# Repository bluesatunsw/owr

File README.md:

# owr
This repo includes all software necessary to operate the Test Rover Platform
that is being designed and developed in the OWR project.
=======

## System Setup
A guide is available on the
[owr-docs](https://github.com/bluesatunsw/owr-docs/tree/main/src/guides/container_setup.md)
repository.

## Useful Command index
| Command                                                               | Effect                                                                                          |
| -------------------------------                                       | --------------------------------                                                                |
| `podman compose -f "$PWD/.devcontainer/docker-compose.yml" up -d`     | Run in the git root to build/restart/start the Docker container.                                |
| `podman compose -f "$PWD/.devcontainer/docker-compose-obc.yml" up -d` | Run in the git root to build/restart/start the Docker container **with obc specific settings!** |
| `podman exec -it --latest /bin/bash`                                  | Enter the docker container after launching it with the devcontainer.                            |
| `./utils/init.bash`                                                   | Run after `cd`'ing into `/workspaces/owr` in the container to source the ROS env and tools      |
| `colcon build --symlink-install`                                      | Runs the `colcon` meta build system, builds ALL rover packages!                                 |
| `ros2 launch rover rover.launch.py`                                   | Launch the robot state publisher. Just leave this running.                                      |
| `rqt`                                                                 | The flexible ROS2 viewer, useful for debugging topic flows and looking at raw topics.           |
| `rviz2`                                                               | Useful for visualizing TF2 / LiDAR / etc... data to see if it looks okay.                       |
| `podman rm --force --latest -t 0`                                     | Kill the podman container with the latest creation date (quickly)                               |

NOTE: `podman compose` will take a VERY long time! on uni Wi-Fi \~5min due to
the amount of packages it installs (\~5GB). There is also [a podman
bug](github.com/containers/podman/issues/16541) that invokes a postprocessing
step on the overlay filesystem, this will take **upwards of 10 minutes!** 

NOTE: `./utils/init.bash` will source the appropriate files as well as put you
in a 10-deep nested shell - running an invalid command will kill 1 level!

### Less Common Commands

| Command                                                               | Effect                                                                                    |
| -------------------------------                                       | --------------------------------                                                          |
| `ros2 launch rover rsp.launch.py`                                     | Robot State Publisher, publishes the URDF+JSP, to make it viewable in Lichtblick / Rviz2. |
| `xacro ./src/rover/description/robot.urdf.xacro > ./build/rover.urdf` | Compiles the xacro into a singular urdf file                                              |
| `ros2 run key_teleop key_teleop --ros-args -p twist_stamped_enabled:=True -r /key_vel:=/diff_drive_base_controller/cmd_vel` | Record keyboard imputs and publish them as Twist2d values, which ROS2Control is listening for!

### Useful Podman Commands
| Command                                                               | Effect                                                                                    |
| -------------------------------                                       | ---------------------------------                                                         |
| `podman images`                                                       | Lists current podman images                                                               |
| `podman rmi {ID} --force`                                             | Remove relevant image. Replace the ID with output from the above command                  |

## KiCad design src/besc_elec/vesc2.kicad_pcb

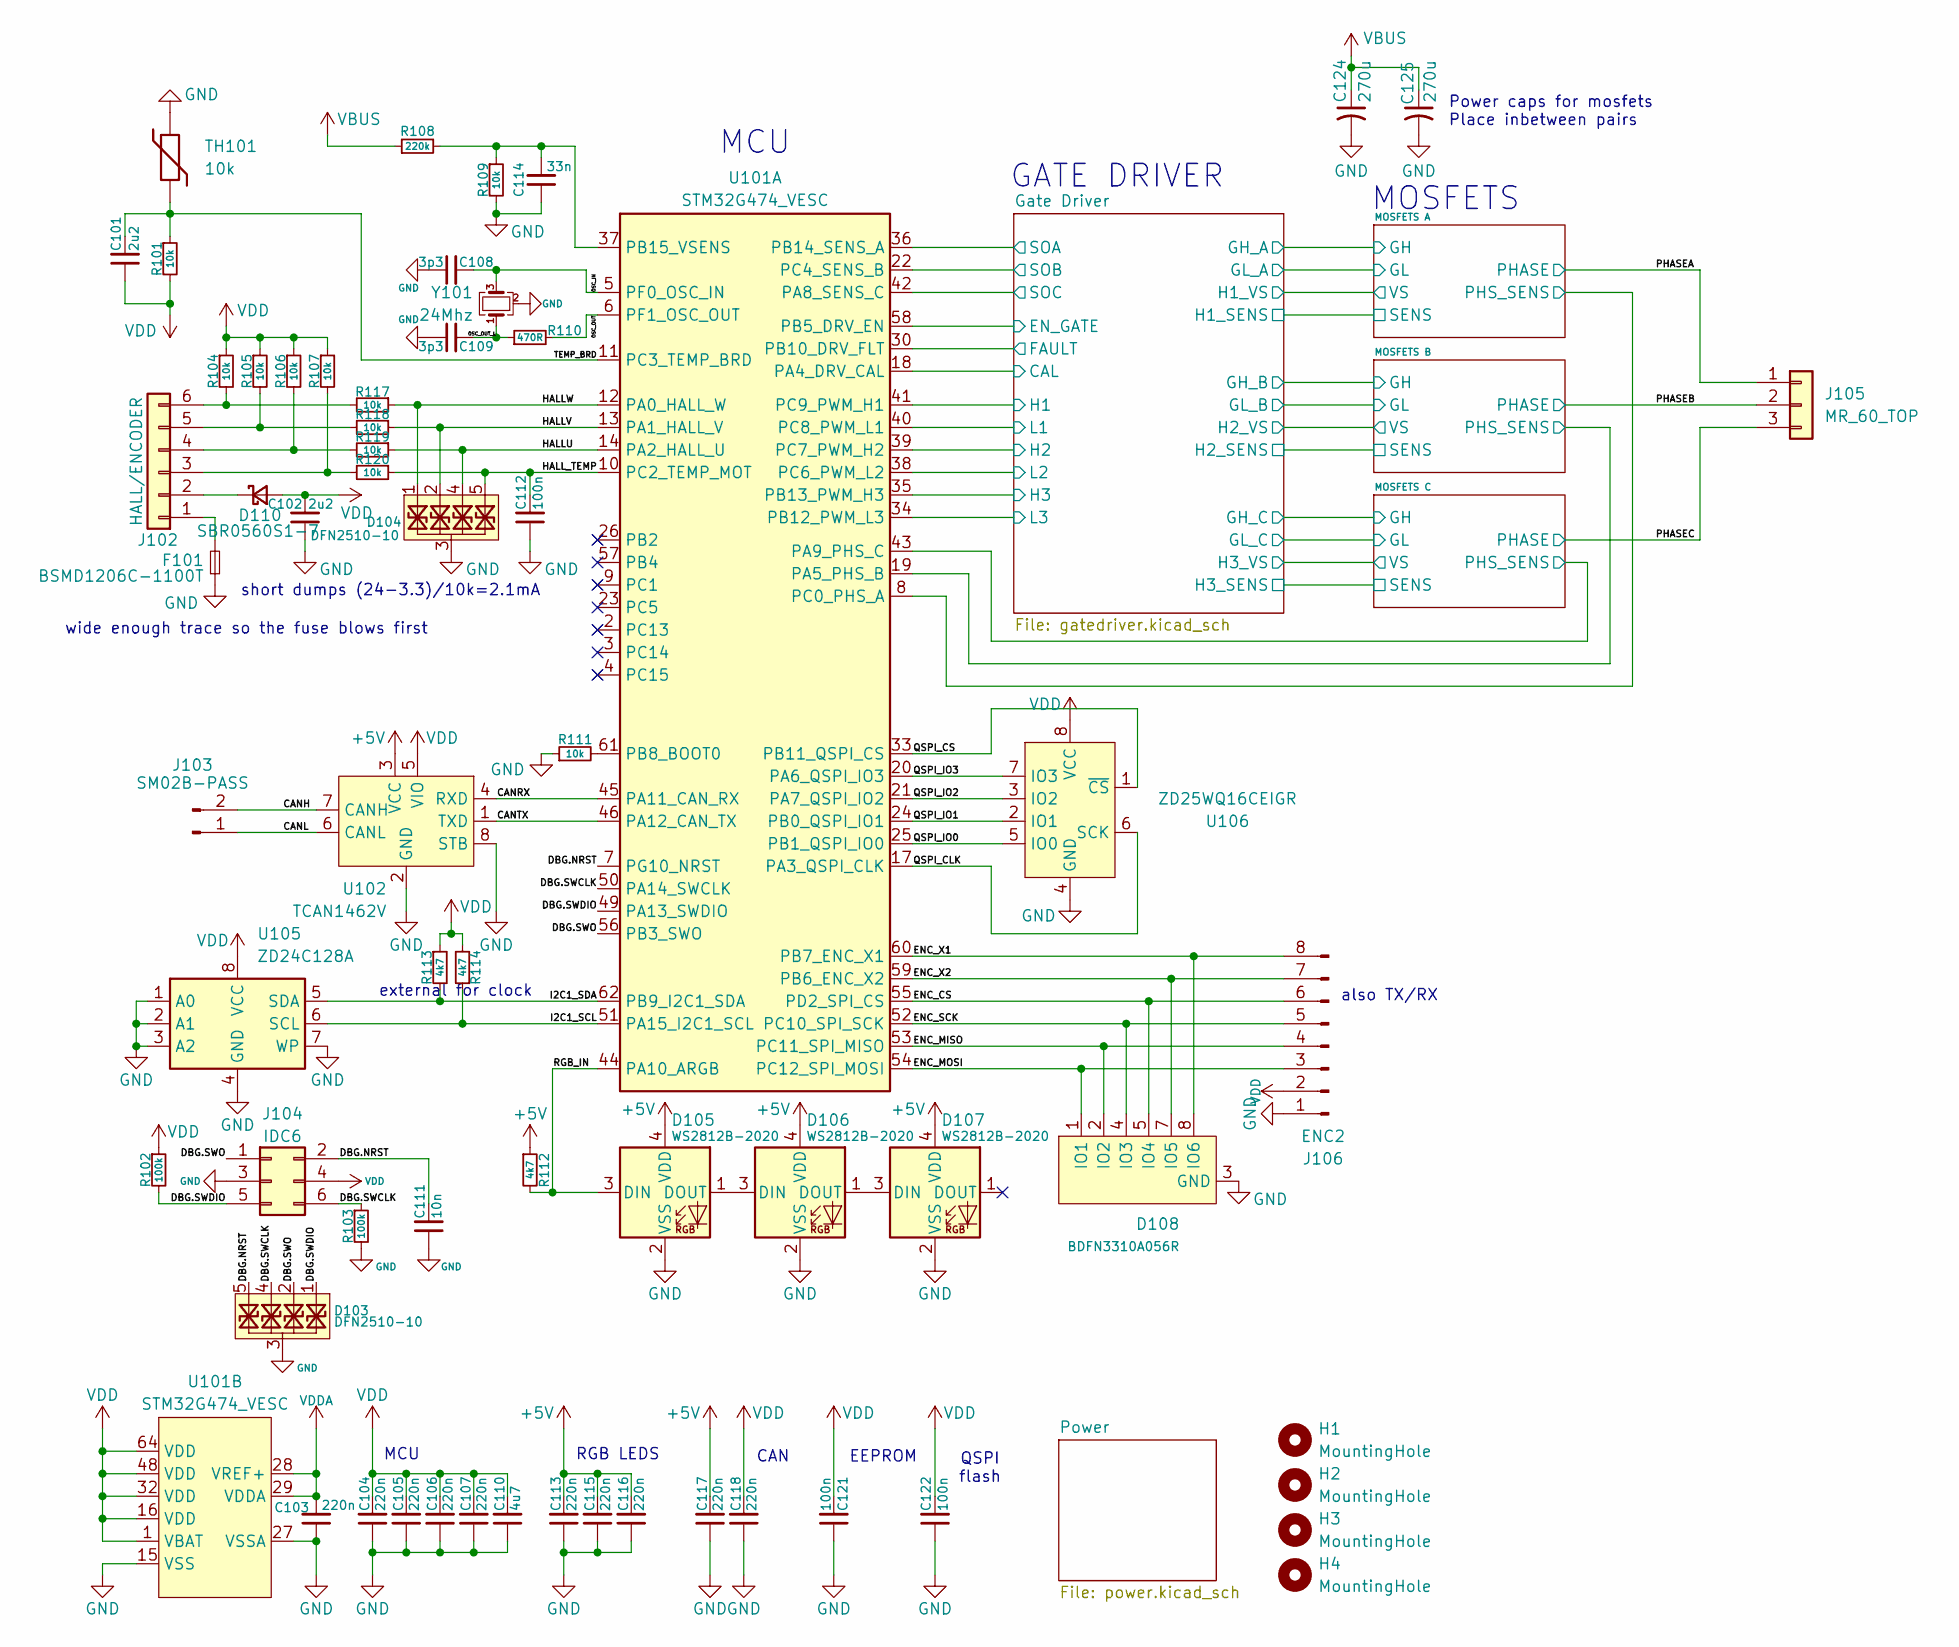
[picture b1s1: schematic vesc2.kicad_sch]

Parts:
C101, C102: 2u2; C_0603_1608Metric
C103, C104, C105, C106, C107, C113, C115, C116, C117, C118: 220n; C_0402_1005Metric
C108, C109: 3p3; C_0402_1005Metric
C110: 4u7; C_0805_2012Metric
C111: 10n; C_0402_1005Metric
C112, C121, C122: 100n; C_0402_1005Metric
C114: 33n; C_0402_1005Metric
C124, C125: 270u; CP_Elec_10x10
D103, D104: DFN2510-10; Diodes_UDFN-10_1x2.5mm_P0.5mm
D105, D106, D107: WS2812B-2020; LED_WS2812B-2020_PLCC4_2.0x2.0mm
D108: BDFN3310A056R; UDFN8_3P3X1_517CB_ONS
D110: SBR0560S1-7; D_SOD-123
F101: BSMD1206C-1100T; Fuse_1206_3216Metric
H1, H2, H3, H4: MountingHole; bluesatM2.5
J102: HALL/ENCODER; BM06B-PASS
J103: SM02B-PASS; BM02B-PASS
J104: IDC6
J105: MR_60_TOP; MR60-F-TopMount
J106: ENC2; JST_PH_B8B-PH-SM4-TB_1x08-1MP_P2.00mm_Vertical
R101, R104, R105, R106, R107, R109, R111, R117, R118, R119, R120: 10k; R_0402_1005Metric
R102, R103: 100k; R_0402_1005Metric
R108: 220k; R_0402_1005Metric
R110: 470R; R_0402_1005Metric
R112, R113, R114: 4k7; R_0402_1005Metric
TH101: 10k; R_0402_1005Metric
U101: STM32G474_VESC; LQFP-64-0.5
U102: TCAN1462V; SOIC-8_3.9x4.9mm_P1.27mm
U105: ZD24C128A; TSSOP-8_4.4x3.0-0.65
U106: ZD25WQ16CEIGR; Winbond_USON-8-1EP_3x2mm_P0.5mm_EP0.2x1.6mm
Y101: 24Mhz; Crystal_SMD_2016-4Pin_2.0x1.6mm

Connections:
+5V: C113.2, C115.2, C116.2, C117.2, D105.4 (VDD), D106.4 (VDD), D107.4 (VDD), R112.1, U102.3 (VCC); also elsewhere on the board
/CANH: J103.2, U102.7 (CANH)
/CANL: J103.1, U102.6 (CANL)
/CANRX: U101.45 (PA11_CAN_RX), U102.4 (RXD)
/CANTX: U101.46 (PA12_CAN_TX), U102.1 (TXD)
/DBG.NRST: C111.2, D103.5, D103.6, J104.2, U101.7 (PG10_NRST)
/DBG.SWCLK: D103.4, D103.7, J104.6, R103.1, U101.50 (PA14_SWCLK)
/DBG.SWDIO: D103.1, D103.10, J104.5, R102.2, U101.49 (PA13_SWDIO)
/DBG.SWO: D103.2, D103.9, J104.1, U101.56 (PB3_SWO)
/ENC_CS: D108.5 (IO4), J106.6, U101.55 (PD2_SPI_CS)
/ENC_MISO: D108.2 (IO2), J106.4, U101.53 (PC11_SPI_MISO)
/ENC_MOSI: D108.1 (IO1), J106.3, U101.54 (PC12_SPI_MOSI)
/ENC_SCK: D108.4 (IO3), J106.5, U101.52 (PC10_SPI_SCK)
/ENC_X1: D108.8 (IO6), J106.8, U101.60 (PB7_ENC_X1)
/ENC_X2: D108.7 (IO5), J106.7, U101.59 (PB6_ENC_X2)
/Gate Driver/CAL: U101.18 (PA4_DRV_CAL); also elsewhere on the board
/Gate Driver/EN_GATE: U101.58 (PB5_DRV_EN); also elsewhere on the board
/Gate Driver/FAULT: U101.30 (PB10_DRV_FLT); also elsewhere on the board
/Gate Driver/H1: U101.41 (PC9_PWM_H1); also elsewhere on the board
/Gate Driver/H2: U101.39 (PC7_PWM_H2); also elsewhere on the board
/Gate Driver/H3: U101.35 (PB13_PWM_H3); also elsewhere on the board
/Gate Driver/L1: U101.40 (PC8_PWM_L1); also elsewhere on the board
/Gate Driver/L2: U101.38 (PC6_PWM_L2); also elsewhere on the board
/Gate Driver/L3: U101.34 (PB12_PWM_L3); also elsewhere on the board
/Gate Driver/SOA: U101.36 (PB14_SENS_A); also elsewhere on the board
/Gate Driver/SOB: U101.22 (PC4_SENS_B); also elsewhere on the board
/Gate Driver/SOC: U101.42 (PA8_SENS_C); also elsewhere on the board
/HALLU: D104.4, D104.7, R119.1, U101.14 (PA2_HALL_U)
/HALLV: D104.2, D104.9, R118.1, U101.13 (PA1_HALL_V)
/HALLW: D104.1, D104.10, R117.1, U101.12 (PA0_HALL_W)
/HALL_TEMP: C112.2, D104.5, D104.6, R120.1, U101.10 (PC2_TEMP_MOT)
/I2C1_SCL: R114.1, U101.51 (PA15_I2C1_SCL), U105.6 (SCL)
/I2C1_SDA: R113.2, U101.62 (PB9_I2C1_SDA), U105.5 (SDA)
/MOSFETS A/PHS_SENS: U101.8 (PC0_PHS_A); also elsewhere on the board
/MOSFETS B/PHS_SENS: U101.19 (PA5_PHS_B); also elsewhere on the board
/MOSFETS C/PHS_SENS: U101.43 (PA9_PHS_C); also elsewhere on the board
/OSC_IN: C108.2, U101.5 (PF0_OSC_IN), Y101.3
/OSC_OUT: R110.2, U101.6 (PF1_OSC_OUT)
/OSC_OUT_L: C109.2, R110.1, Y101.1
/PHASEA: J105.1; also elsewhere on the board
/PHASEB: J105.2; also elsewhere on the board
/PHASEC: J105.3; also elsewhere on the board
/QSPI_CLK: U101.17 (PA3_QSPI_CLK), U106.6 (SCK)
/QSPI_CS: U101.33 (PB11_QSPI_CS), U106.1 (~CS)
/QSPI_IO0: U101.25 (PB1_QSPI_IO0), U106.5 (IO0)
/QSPI_IO1: U101.24 (PB0_QSPI_IO1), U106.2 (IO1)
/QSPI_IO2: U101.21 (PA7_QSPI_IO2), U106.3 (IO2)
/QSPI_IO3: U101.20 (PA6_QSPI_IO3), U106.7 (IO3)
/RGB_IN: D105.3 (DIN), R112.2, U101.44 (PA10_ARGB)
/TEMP_BRD: C101.2, R101.1, TH101.2, U101.11 (PC3_TEMP_BRD)
GND: C102.1, C103.1, C104.1, C105.1, C106.1, C107.1, C108.1, C109.1, C110.1, C111.1, C112.1, C113.1, C114.1, C115.1, C116.1, C117.1, C118.1, C121.1, C122.1, C124.2, C125.2, D103.3, D103.8, D104.3, D104.8, D105.2 (VSS), D106.2 (VSS), D107.2 (VSS), D108.3 (GND), D108.6 (GND), D108.9 (GND), D108.10 (GND), F101.1, J104.3, J106.1, J106.MP (EP), R103.2, R109.2, R111.1, TH101.1, U101.15 (VSS), U101.27 (VSSA), U101.31 (VSS), U101.47 (VSS), U101.63 (VSS), U102.2 (GND), U102.8 (STB), U102.9 (EP), U105.1 (A0), U105.2 (A1), U105.3 (A2), U105.4 (GND), U105.7 (WP), U106.4 (GND), U106.9 (EP), Y101.2 (G), Y101.4 (G); also elsewhere on the board
unnamed: D105.1 (DOUT), D106.3 (DIN)
unnamed: D106.1 (DOUT), D107.3 (DIN)
unnamed: D110.1 (K), J102.2
unnamed: F101.2, J102.1
unnamed: J102.3, R107.2, R120.2
unnamed: J102.4, R106.2, R119.2
unnamed: J102.5, R105.2, R118.2
unnamed: J102.6, R104.2, R117.2
unnamed: R111.2, U101.61 (PB8_BOOT0)
unnamed: C114.2, R108.2, R109.1, U101.37 (PB15_VSENS)
VBUS: C124.1, C125.1, R108.1; also elsewhere on the board
VDD: C101.1, C102.2, C104.2, C105.2, C106.2, C107.2, C110.2, C118.2, C121.2, C122.2, D110.2 (A), J104.4, J106.2, R101.2, R102.1, R104.1, R105.1, R106.1, R107.1, R113.1, R114.2, U101.1 (VBAT), U101.16 (VDD), U101.32 (VDD), U101.48 (VDD), U101.64 (VDD), U102.5 (VIO), U105.8 (VCC), U106.8 (VCC); also elsewhere on the board
VDDA: C103.2, U101.28 (VREF+), U101.29 (VDDA); also elsewhere on the board

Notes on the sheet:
EEPROM
RGB LEDS
Power caps for mosfets Place inbetween pairs
GATE DRIVER
MCU
CAN
also TX/RX
MOSFETS
wide enough trace so the fuse blows first
QSPI flash
external for clock
short dumps (24-3.3)/10k=2.1mA

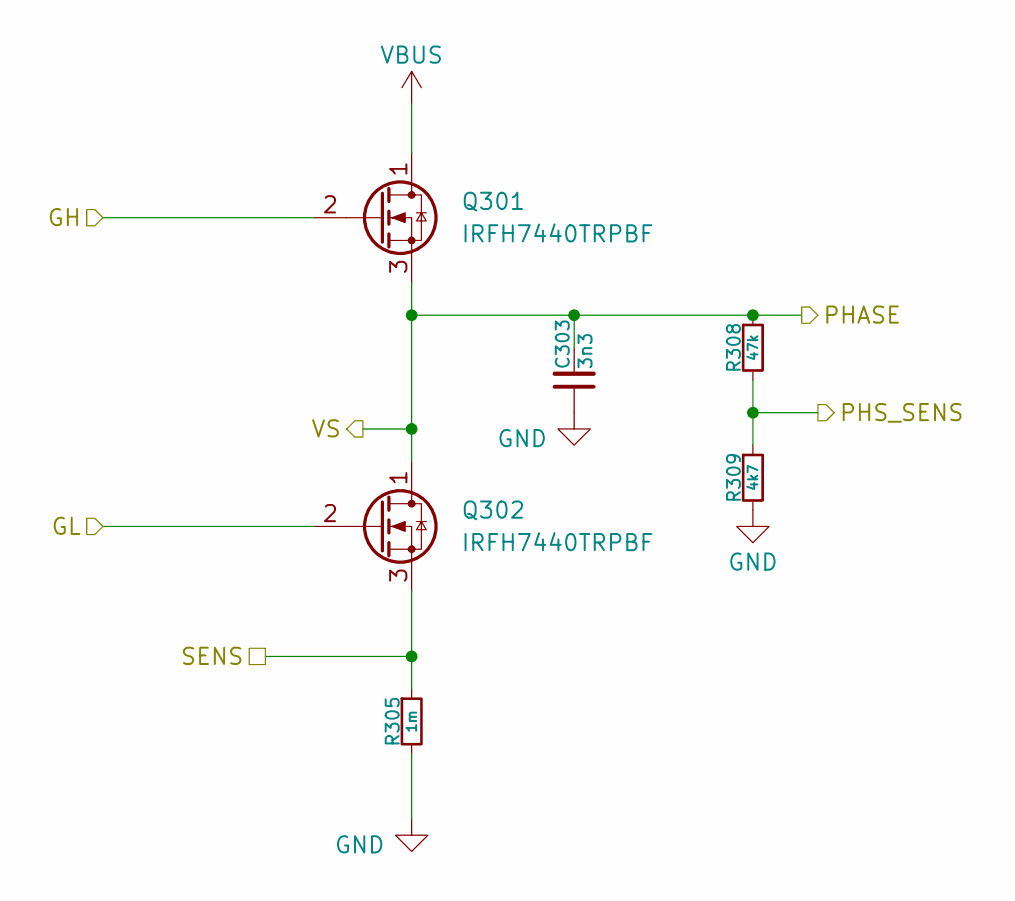
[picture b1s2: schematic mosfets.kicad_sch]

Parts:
C303: 3n3; C_0402_1005Metric
Q301, Q302: IRFH7440TRPBF; PQFN_5x6mm_E_DGS
R305: 1m; R_2512_6332Metric
R308: 47k; R_0402_1005Metric
R309: 4k7; R_0402_1005Metric

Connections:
/Gate Driver/GH_C: Q301.2 (G); also elsewhere on the board
/Gate Driver/GL_C: Q302.2 (G); also elsewhere on the board
/Gate Driver/H3_SENS: Q302.3 (S), R305.1; also elsewhere on the board
/MOSFETS C/PHS_SENS: R308.2, R309.1; also elsewhere on the board
/PHASEC: C303.2, Q301.3 (S), Q302.1 (D), R308.1; also elsewhere on the board
GND: C303.1, R305.2, R309.2; also elsewhere on the board
VBUS: Q301.1 (D); also elsewhere on the board

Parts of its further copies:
C403, C503: 3n3; C_0402_1005Metric
Q401, Q402, Q501, Q502: IRFH7440TRPBF; PQFN_5x6mm_E_DGS
R405, R505: 1m; R_2512_6332Metric
R408, R508: 4k7; R_0402_1005Metric
R409, R509: 47k; R_0402_1005Metric

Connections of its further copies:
/Gate Driver/GH_A: Q501.2 (G); also elsewhere on the board
/Gate Driver/GH_B: Q401.2 (G); also elsewhere on the board
/Gate Driver/GL_A: Q502.2 (G); also elsewhere on the board
/Gate Driver/GL_B: Q402.2 (G); also elsewhere on the board
/Gate Driver/H1_SENS: Q502.3 (S), R505.1; also elsewhere on the board
/Gate Driver/H2_SENS: Q402.3 (S), R405.1; also elsewhere on the board
/MOSFETS A/PHS_SENS: R508.1, R509.2; also elsewhere on the board
/MOSFETS B/PHS_SENS: R408.1, R409.2; also elsewhere on the board
/PHASEA: C503.2, Q501.3 (S), Q502.1 (D), R509.1; also elsewhere on the board
/PHASEB: C403.2, Q401.3 (S), Q402.1 (D), R409.1; also elsewhere on the board
GND: C403.1, C503.1, R405.2, R408.2, R505.2, R508.2; also elsewhere on the board
VBUS: Q401.1 (D), Q501.1 (D); also elsewhere on the board

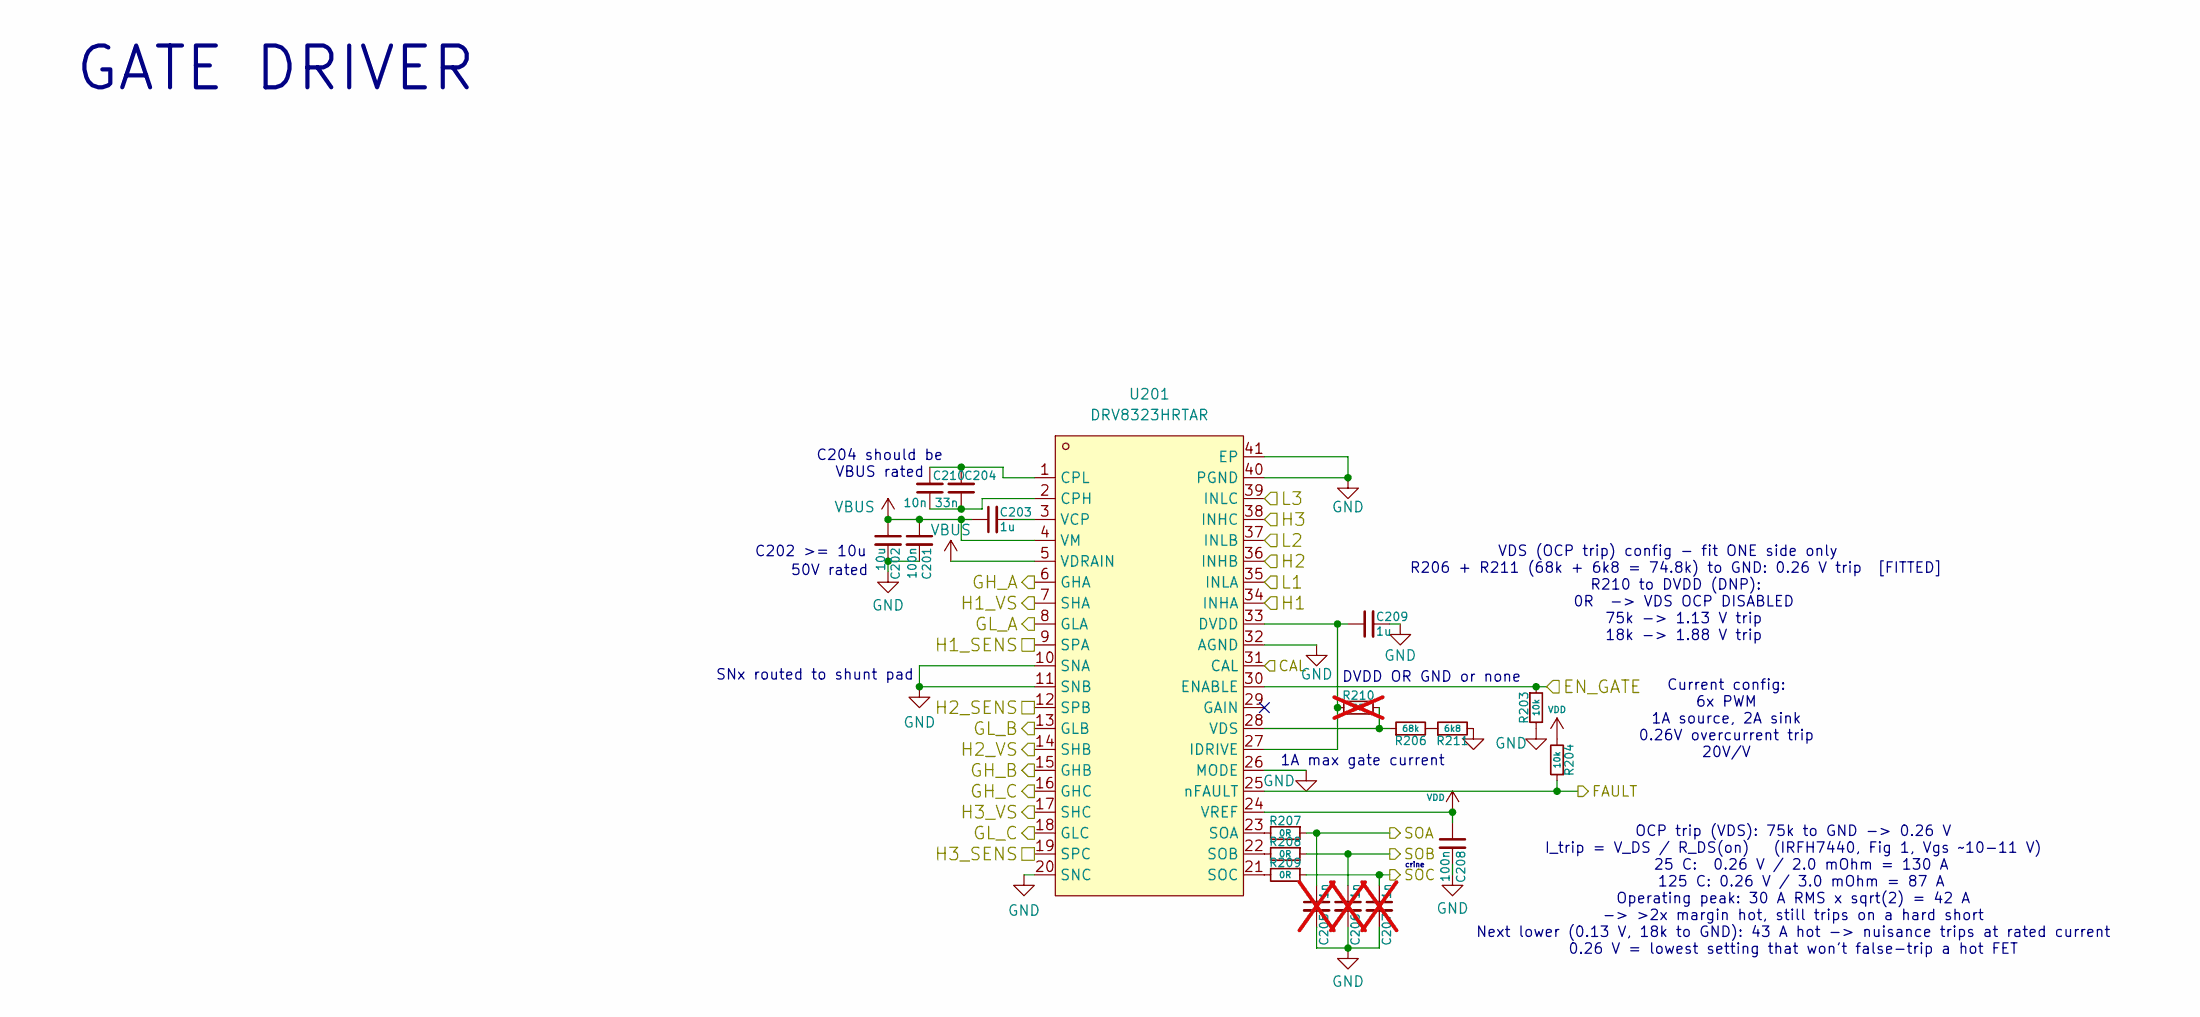
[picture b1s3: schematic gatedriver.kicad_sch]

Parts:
C201: 100n; C_0603_1608Metric
C202: 10u; C_1210_3225Metric
C203: 1u; C_0805_2012Metric
C204: 33n; C_0603_1608Metric
C205, C206, C207: 1n; C_0402_1005Metric; not fitted
C208: 100n; C_0402_1005Metric
C209: 1u; C_0603_1608Metric
C210: 10n; C_0603_1608Metric
R203, R204: 10k; R_0402_1005Metric
R206: 68k; R_0402_1005Metric
R207, R208, R209: 0R; R_0402_1005Metric
R210: 0R; R_0402_1005Metric; not fitted
R211: 6k8; R_0402_1005Metric
U201: DRV8323HRTAR; QFN-40_L6.0-W6.0-P0.50-BL-EP4.5; MPN DRV8323HRTAR; LCSC Part C701783

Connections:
/Gate Driver/CAL: U201.31 (CAL); also elsewhere on the board
/Gate Driver/EN_GATE: R203.1, U201.30 (ENABLE); also elsewhere on the board
/Gate Driver/FAULT: R204.1, U201.25 (nFAULT); also elsewhere on the board
/Gate Driver/GH_A: U201.6 (GHA); also elsewhere on the board
/Gate Driver/GH_B: U201.15 (GHB); also elsewhere on the board
/Gate Driver/GH_C: U201.16 (GHC); also elsewhere on the board
/Gate Driver/GL_A: U201.8 (GLA); also elsewhere on the board
/Gate Driver/GL_B: U201.13 (GLB); also elsewhere on the board
/Gate Driver/GL_C: U201.18 (GLC); also elsewhere on the board
/Gate Driver/H1: U201.34 (INHA); also elsewhere on the board
/Gate Driver/H1_SENS: U201.9 (SPA); also elsewhere on the board
/Gate Driver/H2: U201.36 (INHB); also elsewhere on the board
/Gate Driver/H2_SENS: U201.12 (SPB); also elsewhere on the board
/Gate Driver/H3: U201.38 (INHC); also elsewhere on the board
/Gate Driver/H3_SENS: U201.19 (SPC); also elsewhere on the board
/Gate Driver/L1: U201.35 (INLA); also elsewhere on the board
/Gate Driver/L2: U201.37 (INLB); also elsewhere on the board
/Gate Driver/L3: U201.39 (INLC); also elsewhere on the board
/Gate Driver/SOA: C205.1, R207.1; also elsewhere on the board
/Gate Driver/SOB: C206.1, R208.1; also elsewhere on the board
/Gate Driver/SOC: C207.1, R209.1; also elsewhere on the board
/PHASEA: U201.7 (SHA); also elsewhere on the board
/PHASEB: U201.14 (SHB); also elsewhere on the board
/PHASEC: U201.17 (SHC); also elsewhere on the board
GND: C201.2, C202.2, C205.2, C206.2, C207.2, C208.2, C209.2, R203.2, R211.2, U201.10 (SNA), U201.11 (SNB), U201.20 (SNC), U201.26 (MODE), U201.32 (AGND), U201.40 (PGND), U201.41 (EP); also elsewhere on the board
unnamed: R206.2, R211.1
unnamed: C204.1, C210.1, U201.2 (CPH)
unnamed: C204.2, C210.2, U201.1 (CPL)
unnamed: C209.1, R210.2, U201.27 (IDRIVE), U201.33 (DVDD)
unnamed: R207.2, U201.23 (SOA)
unnamed: R208.2, U201.22 (SOB)
unnamed: R209.2, U201.21 (SOC)
unnamed: C203.2, U201.3 (VCP)
unnamed: R206.1, R210.1, U201.28 (VDS)
VBUS: C201.1, C202.1, C203.1, U201.4 (VM), U201.5 (VDRAIN); also elsewhere on the board
VDD: C208.1, R204.2, U201.24 (VREF); also elsewhere on the board

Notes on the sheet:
C204 should be VBUS rated
GATE DRIVER
OCP trip (VDS): 75k to GND -> 0.26 V I_trip = V_DS / R_DS(on) (IRFH7440, Fig 1, Vgs ~10-11 V) 25 C: 0.26 V / 2.0 mOhm = 130 A 125 C: 0.26 V / 3.0 mOhm = 87 A Operating peak: 30 A RMS x sqrt(2) = 42 A -> >2x margin hot, still trips on a hard short Next lower (0.13 V, 18k to GND): 43 A hot -> nuisanc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
Current config: 6x PWM 1A source, 2A sink 0.26V overcurrent trip 20V/V
DVDD OR GND or none
SNx routed to shunt pad
C202 >= 10u
VDS (OCP trip) config - fit ONE side only R206 + R211 (68k + 6k8 = 74.8k) to GND: 0.26 V trip [FITTED] R210 to DVDD (DNP): 0R -> VDS OCP DISABLED 75k -> 1.13 V trip 18k -> 1.88 V trip
50V rated
crine
1A max gate current

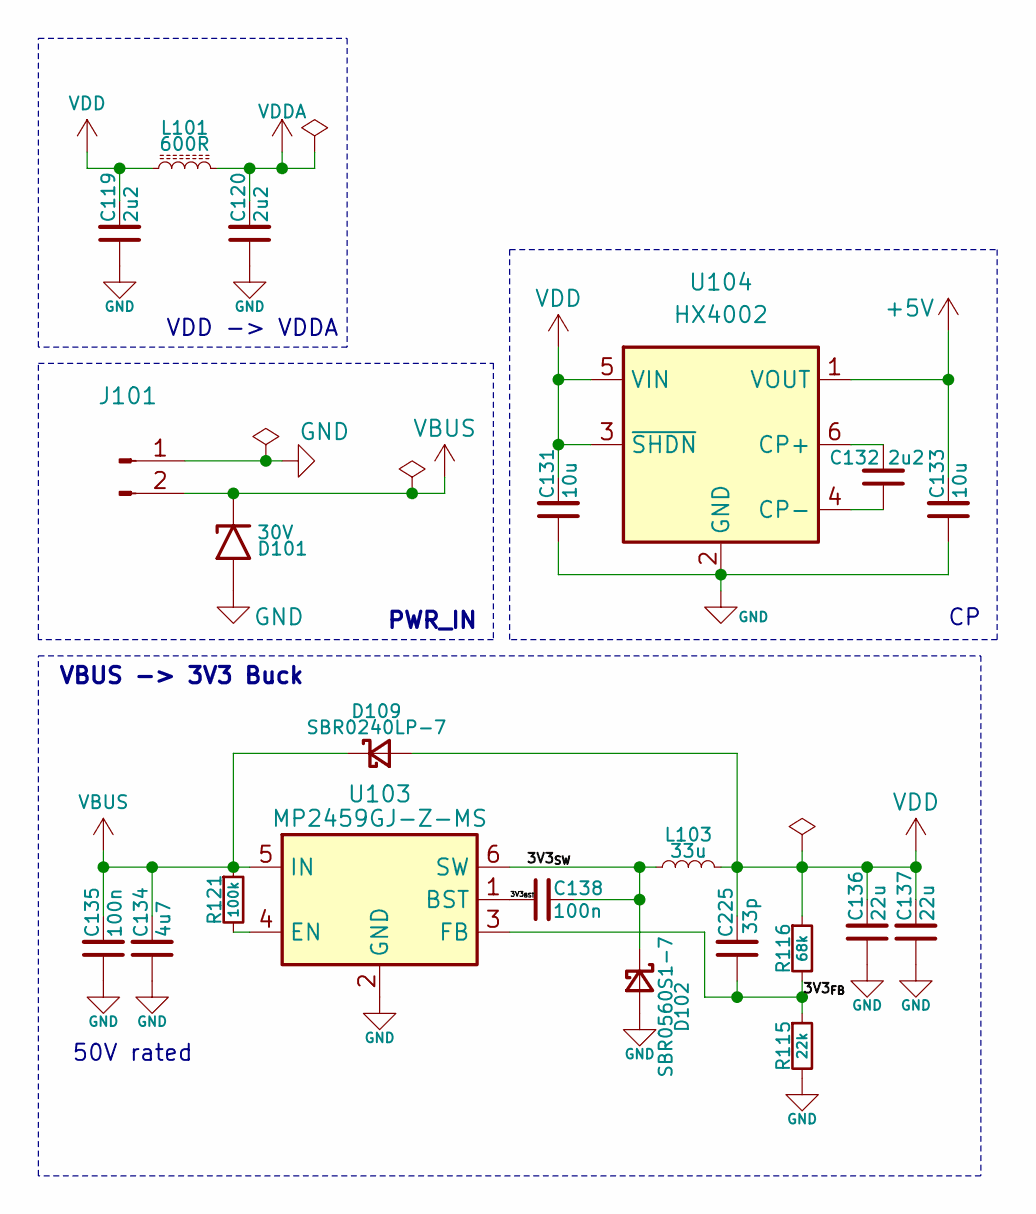
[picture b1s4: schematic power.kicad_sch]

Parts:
C119, C120, C132: 2u2; C_0603_1608Metric
C131, C133: 10u; C_1206_3216Metric
C134: 4u7; C_1210_3225Metric
C135: 100n; C_0603_1608Metric
C136, C137: 22u; C_1210_3225Metric
C138: 100n; C_0402_1005Metric
C225: 33p; C_0402_1005Metric
D101: 30V; D_SMF
D102: SBR0560S1-7; D_SOD-123
D109: SBR0240LP-7; D_SOD-882
J101: XT-30-TOP; AMASS_XT30PW-M_1x02_P2.50mm_Horizontal
L101: 600R; R_0402_1005Metric
L103: 33u; L_Changjiang_FNR5040S
R115: 22k; R_0402_1005Metric
R116: 68k; R_0402_1005Metric
R121: 100k; R_0402_1005Metric
U103: MP2459GJ-Z-MS; TSOT-23-6
U104: HX4002; SOT-23-6

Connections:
+5V: C133.2, U104.1 (VOUT); also elsewhere on the board
/Power/3V3_{BST}: C138.1, U103.1 (BST)
/Power/3V3_{FB}: C225.1, R115.1, R116.2, U103.3 (FB)
/Power/3V3_{SW}: C138.2, D102.1 (K), L103.1, U103.6 (SW)
GND: C119.1, C120.1, C131.1, C133.1, C134.1, C135.1, C136.1, C137.1, D101.2 (A2), D102.2 (A), J101.1, R115.2, U103.2 (GND), U104.2 (GND); also elsewhere on the board
unnamed: R121.2, U103.4 (EN)
unnamed: C132.2, U104.6 (CP+)
unnamed: C132.1, U104.4 (CP-)
VBUS: C134.2, C135.2, D101.1 (A1), D109.1 (K), J101.2, R121.1, U103.5 (IN); also elsewhere on the board
VDD: C119.2, C131.2, C136.2, C137.2, C225.2, D109.2 (A), L101.1, L103.2, R116.1, U104.3 (~SHDN), U104.5 (VIN); also elsewhere on the board
VDDA: C120.2, L101.2; also elsewhere on the board

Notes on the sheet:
50V rated
VBUS -> 3V3 Buck
VDD -> VDDA
PWR_IN

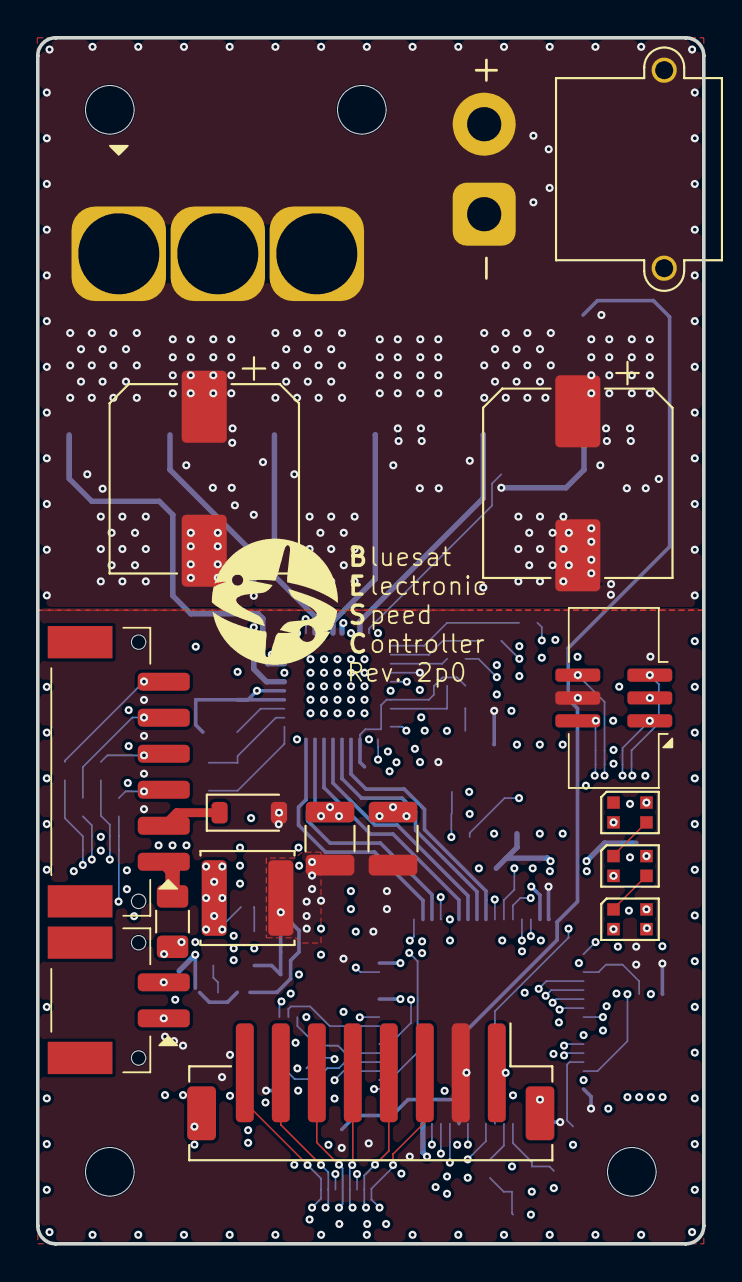
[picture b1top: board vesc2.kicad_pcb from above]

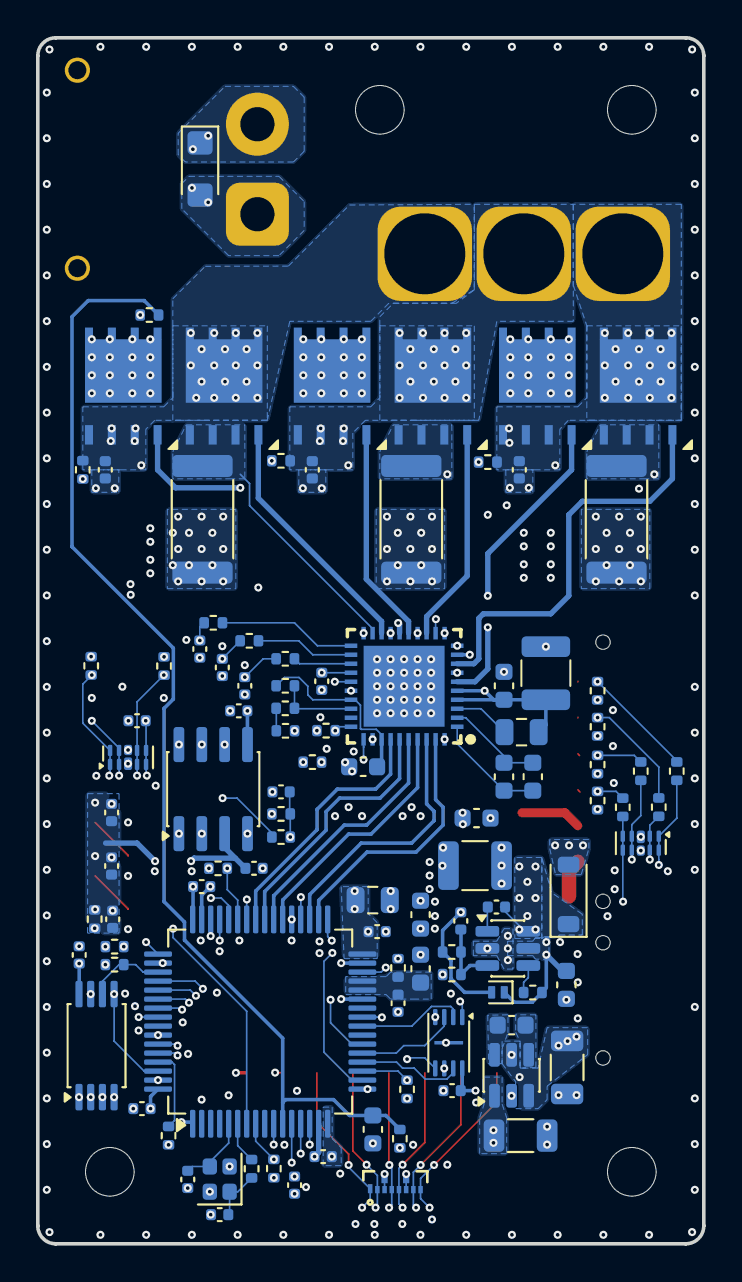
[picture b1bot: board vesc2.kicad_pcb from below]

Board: 6 copper layers, 37.0 x 67.0 mm, 122 parts (102 on the bottom side), 88 nets.

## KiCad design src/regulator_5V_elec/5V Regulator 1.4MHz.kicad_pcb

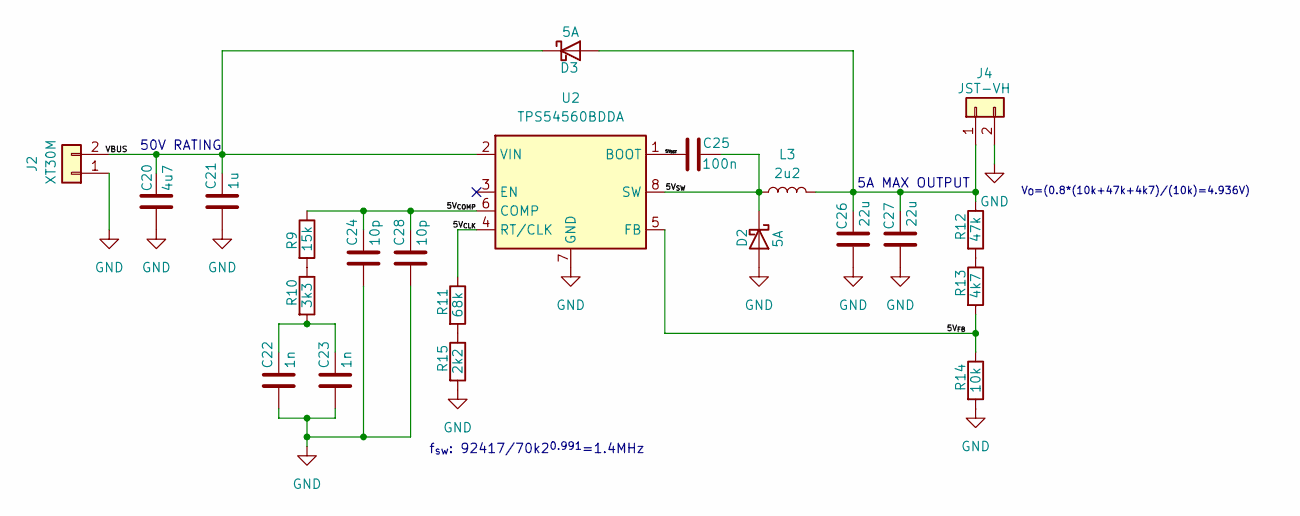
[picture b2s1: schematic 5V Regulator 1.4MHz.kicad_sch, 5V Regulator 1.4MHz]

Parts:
C20: 4u7; C_1210_3225Metric
C21: 1u; C_1206_3216Metric
C22, C23: 1n; C_0402_1005Metric
C24, C28: 10p; C_0402_1005Metric
C25: 100n; C_0402_1005Metric
C26, C27: 22u; C_1210_3225Metric
D2, D3: 5A; D_SMA
J2: XT30M; AMASS_XT30PW-M_1x02_P2.50mm_Horizontal
J4: JST-VH; S2P-VH
L3: 2u2; L_Changjiang_FXL0630
R9: 15k; R_0402_1005Metric
R10: 3k3; R_0402_1005Metric
R11: 68k; R_0402_1005Metric
R12: 47k; R_0402_1005Metric
R13: 4k7; R_0402_1005Metric
R14: 10k; R_0402_1005Metric
R15: 2k2; R_0402_1005Metric
U2: TPS54560BDDA; Texas_R-PDSO-G8_EP2.95x4.9mm_Mask2.4x3.1mm_ThermalVias

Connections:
/5V_{BST}: C25.1, U2.1 (BOOT)
/5V_{CLK}: R11.1, U2.4 (RT/CLK)
/5V_{COMP}: C24.1, C28.1, R9.1, U2.6 (COMP)
/5V_{FB}: R13.2, R14.1, U2.5 (FB)
/5V_{SW}: C25.2, D2.1 (K), L3.1, U2.8 (SW)
/VBUS: C20.1, C21.1, D3.1 (K), J2.2, U2.2 (VIN)
GND: C20.2, C21.2, C22.2, C23.2, C24.2, C26.1, C27.1, C28.2, D2.2 (A), J2.1, J4.2, R14.2, R15.2, U2.7 (GND), U2.9 (GND)
unnamed: C22.1, C23.1, R10.2
unnamed: C26.2, C27.2, D3.2 (A), J4.1, L3.2, R12.1
unnamed: R9.2, R10.1
unnamed: R11.2, R15.1
unnamed: R12.2, R13.1

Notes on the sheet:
5A MAX OUTPUT
V_{O}=(0.8*(10k+47k+4k7)/(10k)=4.936V)
50V RATING
f_{sw}: 92417/70k2^{0.991}=1.4MHz

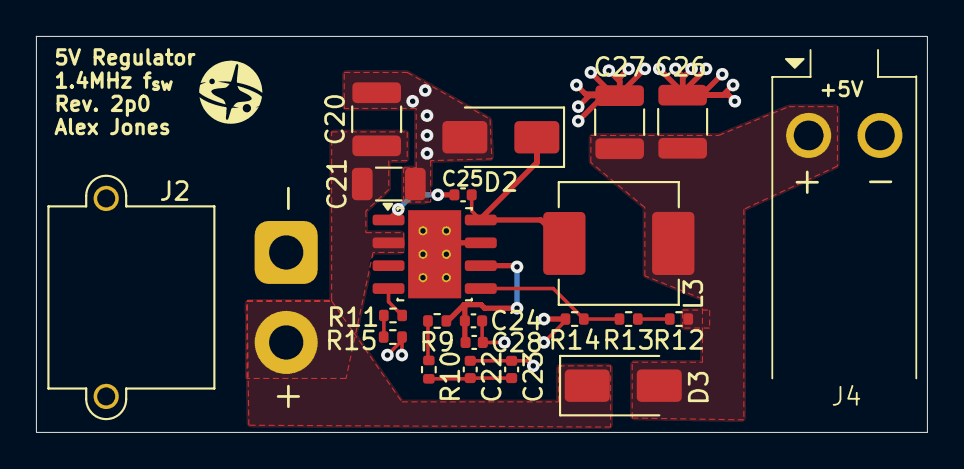
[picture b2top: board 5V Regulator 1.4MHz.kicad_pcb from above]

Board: 2 copper layers, 49.5 x 22.0 mm, 22 parts (0 on the bottom side), 12 nets.

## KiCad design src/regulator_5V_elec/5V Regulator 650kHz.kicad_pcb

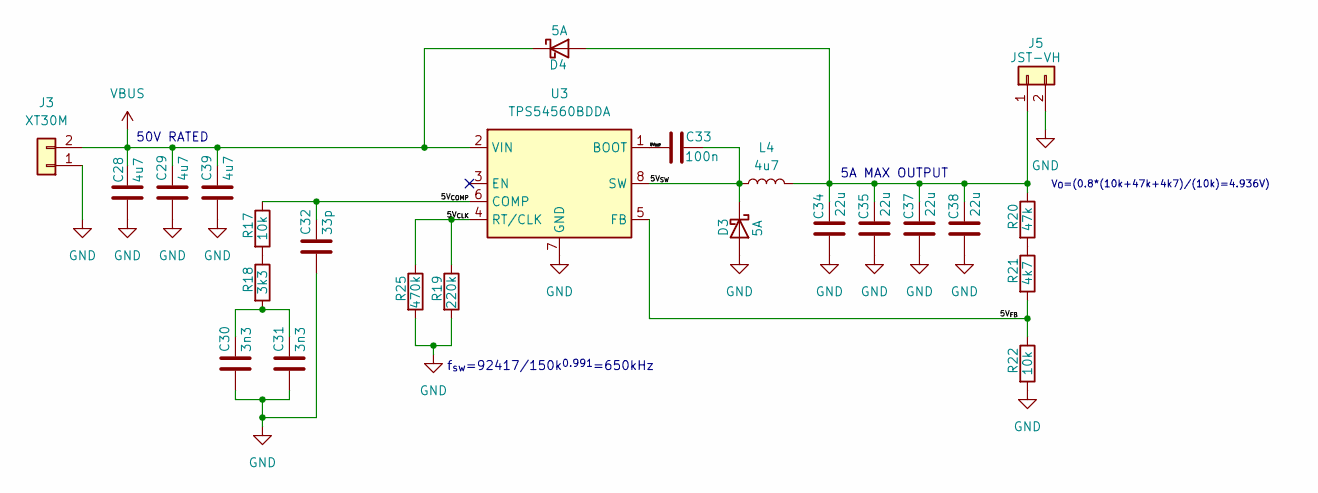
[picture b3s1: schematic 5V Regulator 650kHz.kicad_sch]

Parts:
C28, C29, C39: 4u7; C_1210_3225Metric
C30, C31: 3n3; C_0402_1005Metric
C32: 33p; C_0402_1005Metric
C33: 100n; C_0402_1005Metric
C34, C35, C37, C38: 22u; C_1210_3225Metric
D3, D4: 5A; D_SMA
J3: XT30M; AMASS_XT30PW-M_1x02_P2.50mm_Horizontal
J5: JST-VH; S2P-VH
L4: 4u7; L_Changjiang_FXL1360
R17, R22: 10k; R_0402_1005Metric
R18: 3k3; R_0402_1005Metric
R19: 220k; R_0402_1005Metric
R20: 47k; R_0402_1005Metric
R21: 4k7; R_0402_1005Metric
R25: 470k; R_0402_1005Metric
U3: TPS54560BDDA; Texas_R-PDSO-G8_EP2.95x4.9mm_Mask2.4x3.1mm_ThermalVias

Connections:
/5V_{BST}: C33.1, U3.1 (BOOT)
/5V_{CLK}: R19.1, R25.1, U3.4 (RT/CLK)
/5V_{COMP}: C32.1, R17.1, U3.6 (COMP)
/5V_{FB}: R21.2, R22.1, U3.5 (FB)
/5V_{SW}: C33.2, D3.1 (K), L4.1, U3.8 (SW)
GND: C28.2, C29.2, C30.2, C31.2, C32.2, C34.1, C35.1, C37.1, C38.1, C39.2, D3.2 (A), J3.1, J5.2, R19.2, R22.2, R25.2, U3.7 (GND), U3.9 (GND); also elsewhere on the board
unnamed: C30.1, C31.1, R18.2
unnamed 7: C34.2, C35.2, C37.2, C38.2, D4.2 (A), J5.1, L4.2, R20.1; also elsewhere on the board
unnamed: R17.2, R18.1
unnamed: R20.2, R21.1
VBUS: C28.1, C29.1, C39.1, D4.1 (K), J3.2, U3.2 (VIN); also elsewhere on the board

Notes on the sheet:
5A MAX OUTPUT
f_{sw}=92417/150k^{0.991}=650kHz
50V RATED
V_{O}=(0.8*(10k+47k+4k7)/(10k)=4.936V)

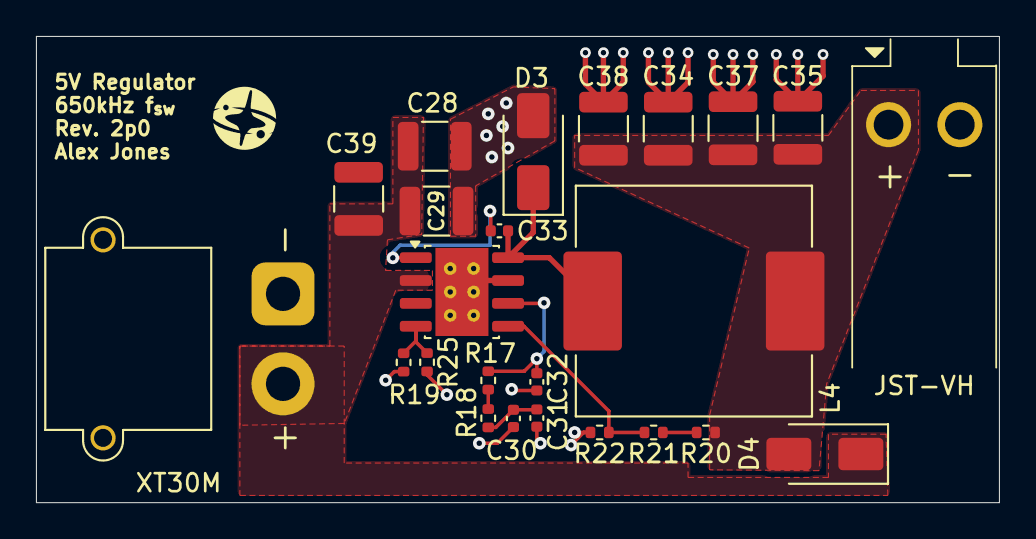
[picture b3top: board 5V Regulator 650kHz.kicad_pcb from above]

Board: 2 copper layers, 53.5 x 25.9 mm, 24 parts (0 on the bottom side), 11 nets.

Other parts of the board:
JST-VH: JST-VH; S2P-VH
XT30M: XT30M; AMASS_XT30PW-M_1x02_P2.50mm_Horizontal

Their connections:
GND: JST-VH.2, XT30M.1; also elsewhere on the board
unnamed 7: JST-VH.1; also elsewhere on the board
VBUS: XT30M.2; also elsewhere on the board
